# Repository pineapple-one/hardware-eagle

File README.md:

# hardware-eagle
Hardware design files in Autodesk Eagle

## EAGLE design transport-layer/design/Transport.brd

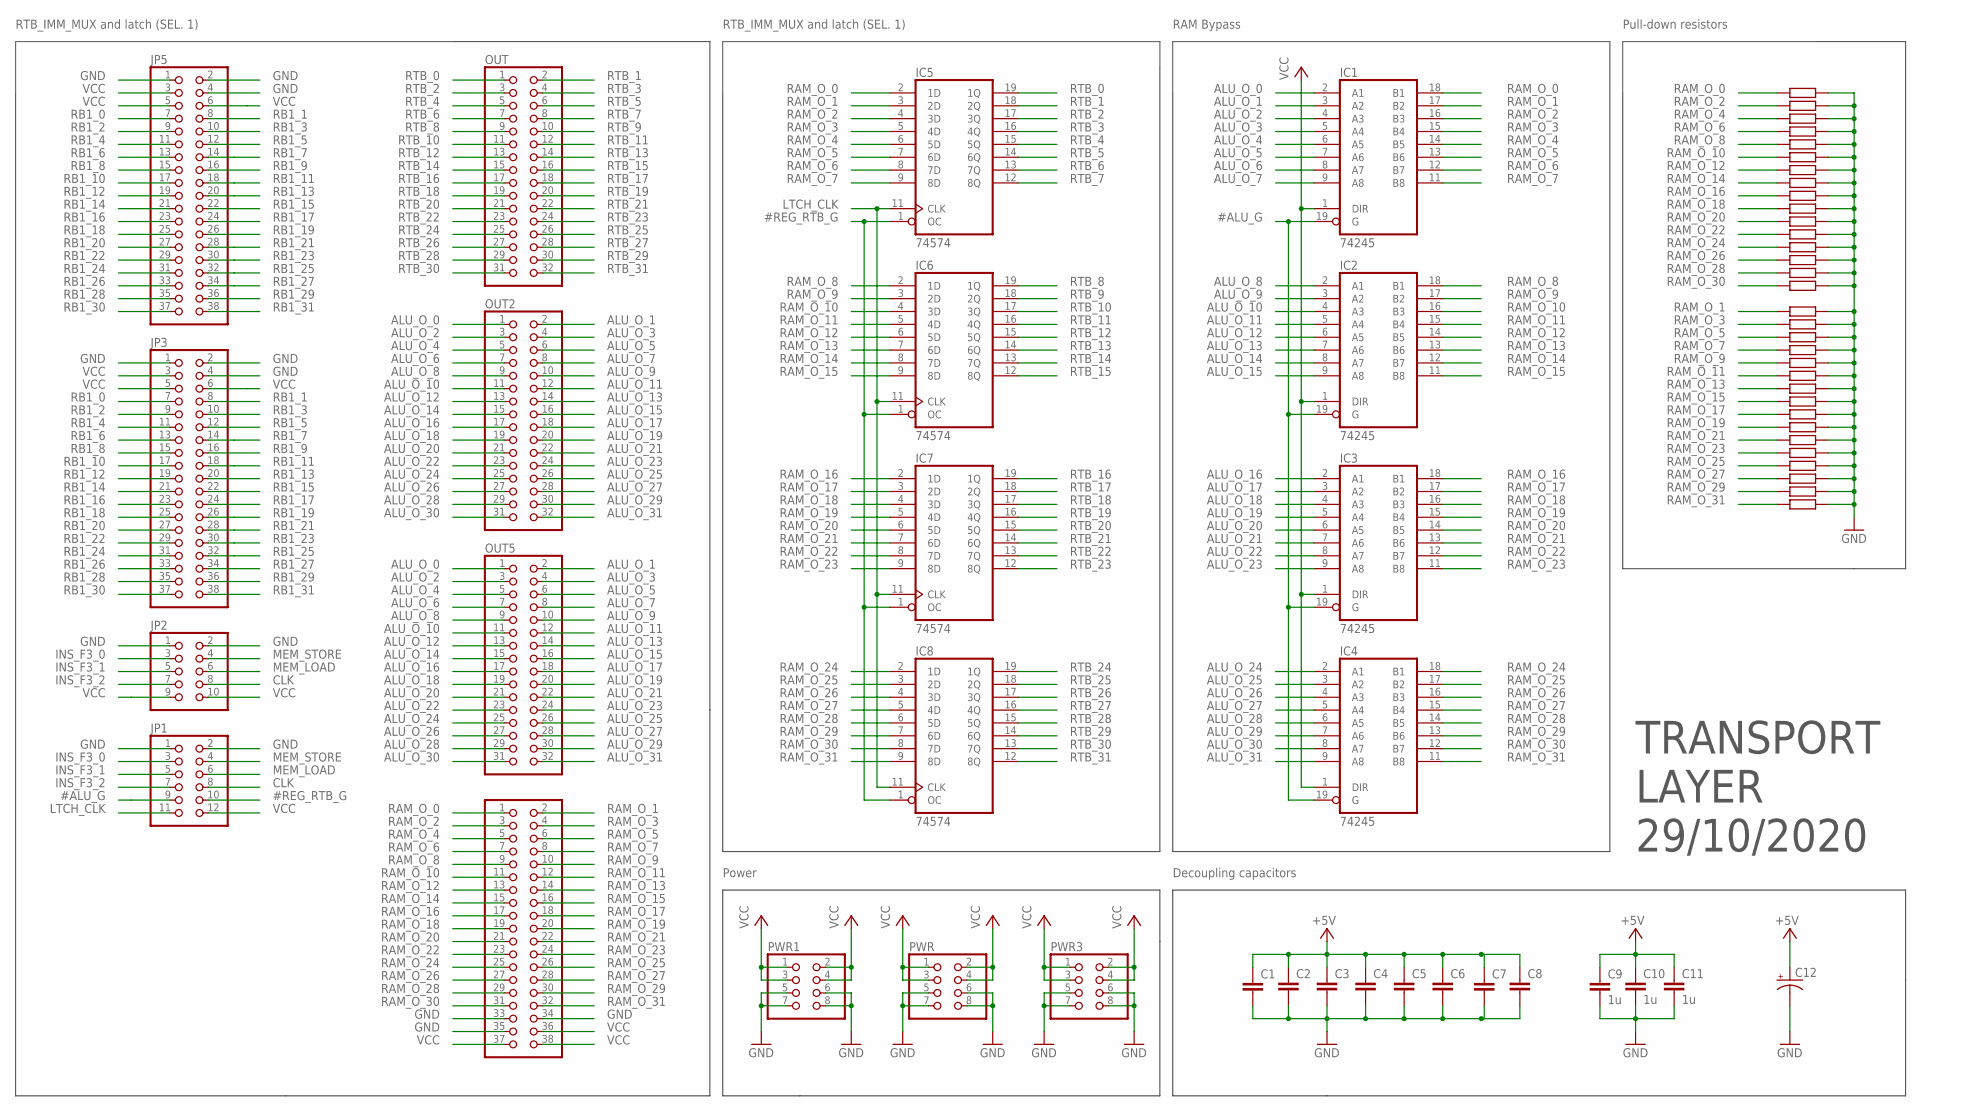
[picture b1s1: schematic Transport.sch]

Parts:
C1, C2, C3, C4, C5, C6, C7, C8: C-EUC0805; C0805
C9, C10, C11: 1u; C0805
C12: CAPACITOR-P153CLV-1010; 153CLV-1010
IC1, IC2, IC3, IC4: 74245; TSSOP20
IC5, IC6, IC7, IC8: 74574; TSSOP20
JP1: PINHD-2X6; 2X06
JP2: PINHD-2X5; 2X05
JP3, JP4, JP5: PINHD-2X19; 2X19
OUT, OUT2, OUT5: PINHD-2X16; 2X16
PWR, PWR1, PWR3: PINHD-2X4; 2X04
R1, R2, R3, R4, R5, R6, R7, R8, R9, R10, R11, R12, R13, R14, R15, R16, R17, R18, R19, R20, R21, R22, R23, R24, R25, R26, R27, R28, R29, R30, R31, R33: R-EU_R0805; R0805

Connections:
#ALU_G: IC1.19 (G), IC2.19 (G), IC3.19 (G), IC4.19 (G), JP1.9
#REG_RTB_G: IC5.1 (OC), IC6.1 (OC), IC7.1 (OC), IC8.1 (OC), JP1.10
ALU_O_0: IC1.2 (A1), OUT2.1, OUT5.1
ALU_O_1: IC1.3 (A2), OUT2.2, OUT5.2
ALU_O_2: IC1.4 (A3), OUT2.3, OUT5.3
ALU_O_3: IC1.5 (A4), OUT2.4, OUT5.4
ALU_O_4: IC1.6 (A5), OUT2.5, OUT5.5
ALU_O_5: IC1.7 (A6), OUT2.6, OUT5.6
ALU_O_6: IC1.8 (A7), OUT2.7, OUT5.7
ALU_O_7: IC1.9 (A8), OUT2.8, OUT5.8
ALU_O_8: IC2.2 (A1), OUT2.9, OUT5.9
ALU_O_9: IC2.3 (A2), OUT2.10, OUT5.10
ALU_O_10: IC2.4 (A3), OUT2.11, OUT5.11
ALU_O_11: IC2.5 (A4), OUT2.12, OUT5.12
ALU_O_12: IC2.6 (A5), OUT2.13, OUT5.13
ALU_O_13: IC2.7 (A6), OUT2.14, OUT5.14
ALU_O_14: IC2.8 (A7), OUT2.15, OUT5.15
ALU_O_15: IC2.9 (A8), OUT2.16, OUT5.16
ALU_O_16: IC3.2 (A1), OUT2.17, OUT5.17
ALU_O_17: IC3.3 (A2), OUT2.18, OUT5.18
ALU_O_18: IC3.4 (A3), OUT2.19, OUT5.19
ALU_O_19: IC3.5 (A4), OUT2.20, OUT5.20
ALU_O_20: IC3.6 (A5), OUT2.21, OUT5.21
ALU_O_21: IC3.7 (A6), OUT2.22, OUT5.22
ALU_O_22: IC3.8 (A7), OUT2.23, OUT5.23
ALU_O_23: IC3.9 (A8), OUT2.24, OUT5.24
ALU_O_24: IC4.2 (A1), OUT2.25, OUT5.25
ALU_O_25: IC4.3 (A2), OUT2.26, OUT5.26
ALU_O_26: IC4.4 (A3), OUT2.27, OUT5.27
ALU_O_27: IC4.5 (A4), OUT2.28, OUT5.28
ALU_O_28: IC4.6 (A5), OUT2.29, OUT5.29
ALU_O_29: IC4.7 (A6), OUT2.30, OUT5.30
ALU_O_30: IC4.8 (A7), OUT2.31, OUT5.31
ALU_O_31: IC4.9 (A8), OUT2.32, OUT5.32
CLK: JP1.8, JP2.8
GND: C1.2, C2.2, C3.2, C4.2, C5.2, C6.2, C7.2, C8.2, C9.2, C10.2, C11.2, C12.-, IC1.10 (GND), IC2.10 (GND), IC3.10 (GND), IC4.10 (GND), IC5.10 (GND), IC6.10 (GND), IC7.10 (GND), IC8.10 (GND), JP1.1, JP1.2, JP2.1, JP2.2, JP3.1, JP3.2, JP3.4, JP4.33, JP4.34, JP4.35, JP5.1, JP5.2, JP5.4, PWR.5, PWR.6, PWR.7, PWR.8, PWR1.5, PWR1.6, PWR1.7, PWR1.8, PWR3.5, PWR3.6, PWR3.7, PWR3.8, R1.2, R2.2, R3.2, R4.2, R5.2, R6.2, R7.2, R8.2, R9.2, R10.2, R11.2, R12.2, R13.2, R14.2, R15.2, R16.2, R17.2, R18.2, R19.2, R20.2, R21.2, R22.2, R23.2, R24.2, R25.2, R26.2, R27.2, R28.2, R29.2, R30.2, R31.2, R33.2
INS_F3_0: JP1.3, JP2.3
INS_F3_1: JP1.5, JP2.5
INS_F3_2: JP1.7, JP2.7
LTCH_CLK: IC5.11 (CLK), IC6.11 (CLK), IC7.11 (CLK), IC8.11 (CLK), JP1.11
MEM_LOAD: JP1.6, JP2.6
MEM_STORE: JP1.4, JP2.4
RAM_O_0: IC1.18 (B1), IC5.2 (1D), JP4.1, R33.1
RAM_O_1: IC1.17 (B2), IC5.3 (2D), JP4.2, R16.1
RAM_O_2: IC1.16 (B3), IC5.4 (3D), JP4.3, R1.1
RAM_O_3: IC1.15 (B4), IC5.5 (4D), JP4.4, R17.1
RAM_O_4: IC1.14 (B5), IC5.6 (5D), JP4.5, R2.1
RAM_O_5: IC1.13 (B6), IC5.7 (6D), JP4.6, R18.1
RAM_O_6: IC1.12 (B7), IC5.8 (7D), JP4.7, R3.1
RAM_O_7: IC1.11 (B8), IC5.9 (8D), JP4.8, R19.1
RAM_O_8: IC2.18 (B1), IC6.2 (1D), JP4.9, R4.1
RAM_O_9: IC2.17 (B2), IC6.3 (2D), JP4.10, R20.1
RAM_O_10: IC2.16 (B3), IC6.4 (3D), JP4.11, R5.1
RAM_O_11: IC2.15 (B4), IC6.5 (4D), JP4.12, R21.1
RAM_O_12: IC2.14 (B5), IC6.6 (5D), JP4.13, R6.1
RAM_O_13: IC2.13 (B6), IC6.7 (6D), JP4.14, R22.1
RAM_O_14: IC2.12 (B7), IC6.8 (7D), JP4.15, R7.1
RAM_O_15: IC2.11 (B8), IC6.9 (8D), JP4.16, R23.1
RAM_O_16: IC3.18 (B1), IC7.2 (1D), JP4.17, R8.1
RAM_O_17: IC3.17 (B2), IC7.3 (2D), JP4.18, R24.1
RAM_O_18: IC3.16 (B3), IC7.4 (3D), JP4.19, R9.1
RAM_O_19: IC3.15 (B4), IC7.5 (4D), JP4.20, R25.1
RAM_O_20: IC3.14 (B5), IC7.6 (5D), JP4.21, R10.1
RAM_O_21: IC3.13 (B6), IC7.7 (6D), JP4.22, R26.1
RAM_O_22: IC3.12 (B7), IC7.8 (7D), JP4.23, R11.1
RAM_O_23: IC3.11 (B8), IC7.9 (8D), JP4.24, R27.1
RAM_O_24: IC4.18 (B1), IC8.2 (1D), JP4.25, R12.1
RAM_O_25: IC4.17 (B2), IC8.3 (2D), JP4.26, R28.1
RAM_O_26: IC4.16 (B3), IC8.4 (3D), JP4.27, R13.1
RAM_O_27: IC4.15 (B4), IC8.5 (4D), JP4.28, R29.1
RAM_O_28: IC4.14 (B5), IC8.6 (5D), JP4.29, R14.1
RAM_O_29: IC4.13 (B6), IC8.7 (6D), JP4.30, R30.1
RAM_O_30: IC4.12 (B7), IC8.8 (7D), JP4.31, R15.1
RAM_O_31: IC4.11 (B8), IC8.9 (8D), JP4.32, R31.1
RB1_0: JP3.7, JP5.7
RB1_1: JP3.8, JP5.8
RB1_2: JP3.9, JP5.9
RB1_3: JP3.10, JP5.10
RB1_4: JP3.11, JP5.11
RB1_5: JP3.12, JP5.12
RB1_6: JP3.13, JP5.13
RB1_7: JP3.14, JP5.14
RB1_8: JP3.15, JP5.15
RB1_9: JP3.16, JP5.16
RB1_10: JP3.17, JP5.17
RB1_11: JP3.18, JP5.18
RB1_12: JP3.19, JP5.19
RB1_13: JP3.20, JP5.20
RB1_14: JP3.21, JP5.21
RB1_15: JP3.22, JP5.22
RB1_16: JP3.23, JP5.23
RB1_17: JP3.24, JP5.24
RB1_18: JP3.25, JP5.25
RB1_19: JP3.26, JP5.26
RB1_20: JP3.27, JP5.27
RB1_21: JP3.28, JP5.28
RB1_22: JP3.29, JP5.29
RB1_23: JP3.30, JP5.30
RB1_24: JP3.31, JP5.31
RB1_25: JP3.32, JP5.32
RB1_26: JP3.33, JP5.33
RB1_27: JP3.34, JP5.34
RB1_28: JP3.35, JP5.35
RB1_29: JP3.36, JP5.36
RB1_30: JP3.37, JP5.37
RB1_31: JP3.38, JP5.38
RTB_0: IC5.19 (1Q), OUT.1
RTB_1: IC5.18 (2Q), OUT.2
RTB_2: IC5.17 (3Q), OUT.3
RTB_3: IC5.16 (4Q), OUT.4
RTB_4: IC5.15 (5Q), OUT.5
RTB_5: IC5.14 (6Q), OUT.6
RTB_6: IC5.13 (7Q), OUT.7
RTB_7: IC5.12 (8Q), OUT.8
RTB_8: IC6.19 (1Q), OUT.9
RTB_9: IC6.18 (2Q), OUT.10
RTB_10: IC6.17 (3Q), OUT.11
RTB_11: IC6.16 (4Q), OUT.12
RTB_12: IC6.15 (5Q), OUT.13
RTB_13: IC6.14 (6Q), OUT.14
RTB_14: IC6.13 (7Q), OUT.15
RTB_15: IC6.12 (8Q), OUT.16
RTB_16: IC7.19 (1Q), OUT.17
RTB_17: IC7.18 (2Q), OUT.18
RTB_18: IC7.17 (3Q), OUT.19
RTB_19: IC7.16 (4Q), OUT.20
RTB_20: IC7.15 (5Q), OUT.21
RTB_21: IC7.14 (6Q), OUT.22
RTB_22: IC7.13 (7Q), OUT.23
RTB_23: IC7.12 (8Q), OUT.24
RTB_24: IC8.19 (1Q), OUT.25
RTB_25: IC8.18 (2Q), OUT.26
RTB_26: IC8.17 (3Q), OUT.27
RTB_27: IC8.16 (4Q), OUT.28
RTB_28: IC8.15 (5Q), OUT.29
RTB_29: IC8.14 (6Q), OUT.30
RTB_30: IC8.13 (7Q), OUT.31
RTB_31: IC8.12 (8Q), OUT.32
VCC: C1.1, C2.1, C3.1, C4.1, C5.1, C6.1, C7.1, C8.1, C9.1, C10.1, C11.1, C12.+, IC1.1 (DIR), IC1.20 (VCC), IC2.1 (DIR), IC2.20 (VCC), IC3.1 (DIR), IC3.20 (VCC), IC4.1 (DIR), IC4.20 (VCC), IC5.20 (VCC), IC6.20 (VCC), IC7.20 (VCC), IC8.20 (VCC), JP1.12, JP2.9, JP2.10, JP3.3, JP3.5, JP3.6, JP4.36, JP4.37, JP4.38, JP5.3, JP5.5, JP5.6, PWR.1, PWR.2, PWR.3, PWR.4, PWR1.1, PWR1.2, PWR1.3, PWR1.4, PWR3.1, PWR3.2, PWR3.3, PWR3.4

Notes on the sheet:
RTB_IMM_MUX and latch (SEL. 1)
RAM Bypass
Pull-down resistors
Power
Decoupling capacitors
TRANSPORT LAYER 29/10/2020

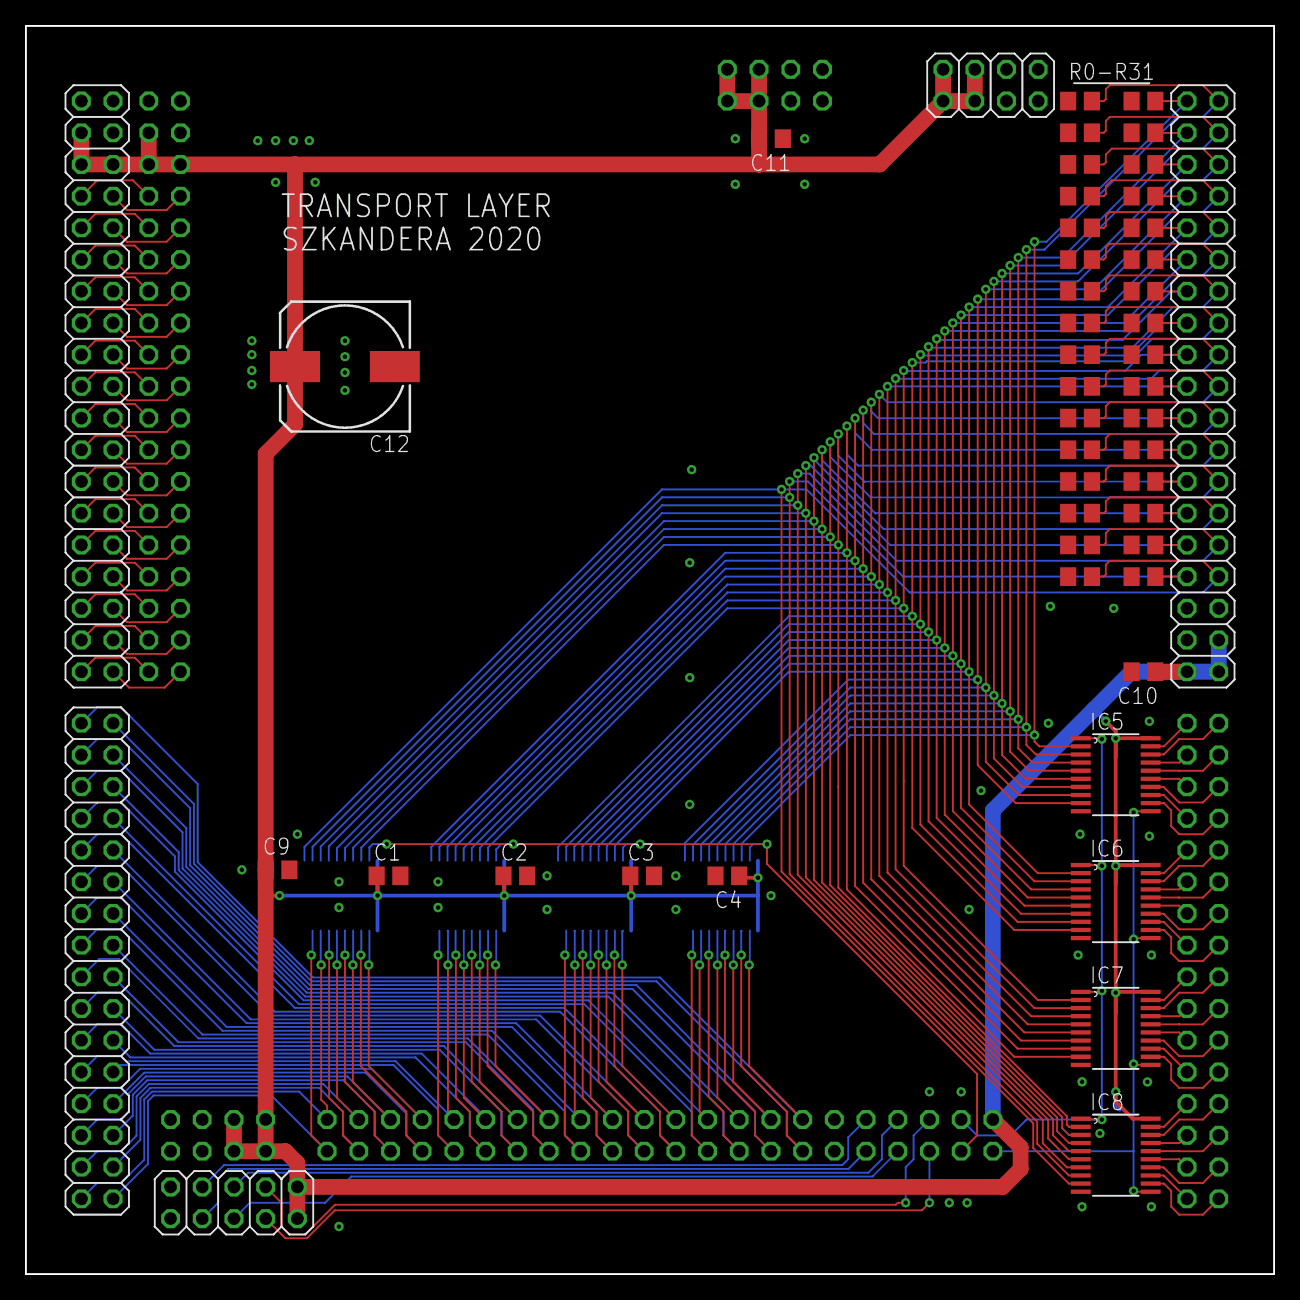
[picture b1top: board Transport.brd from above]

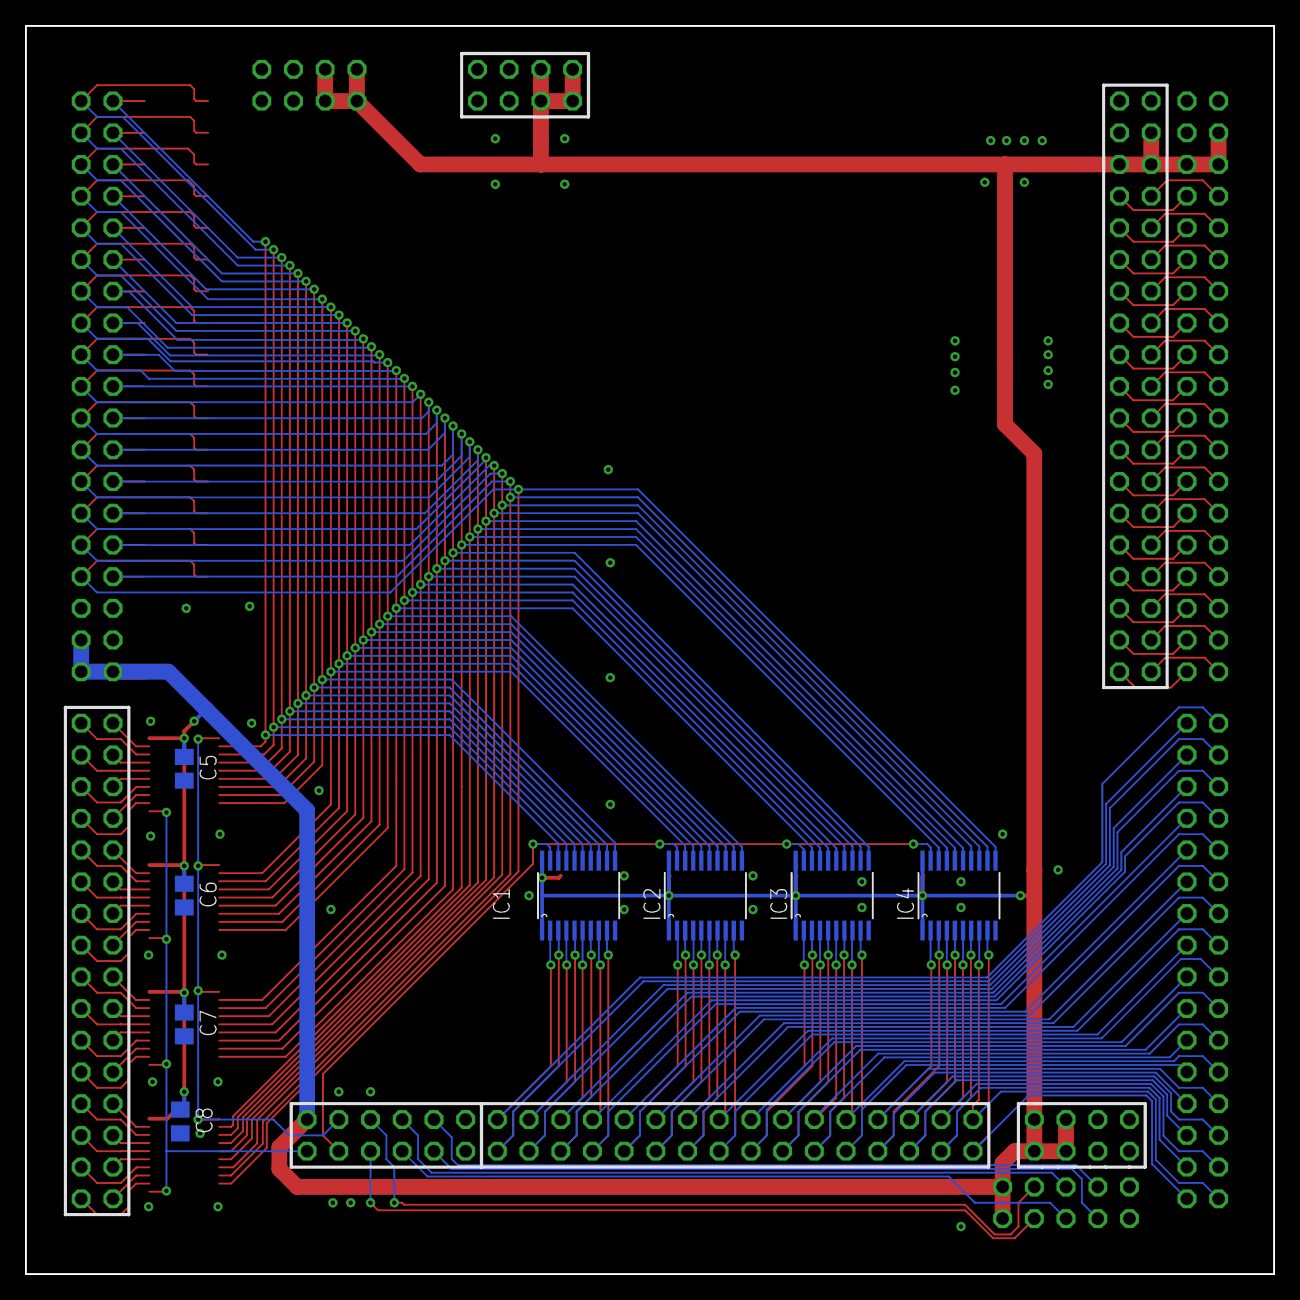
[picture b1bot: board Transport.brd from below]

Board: 2 copper layers, 100.0 x 100.0 mm, 63 parts (8 on the bottom side), 139 nets.

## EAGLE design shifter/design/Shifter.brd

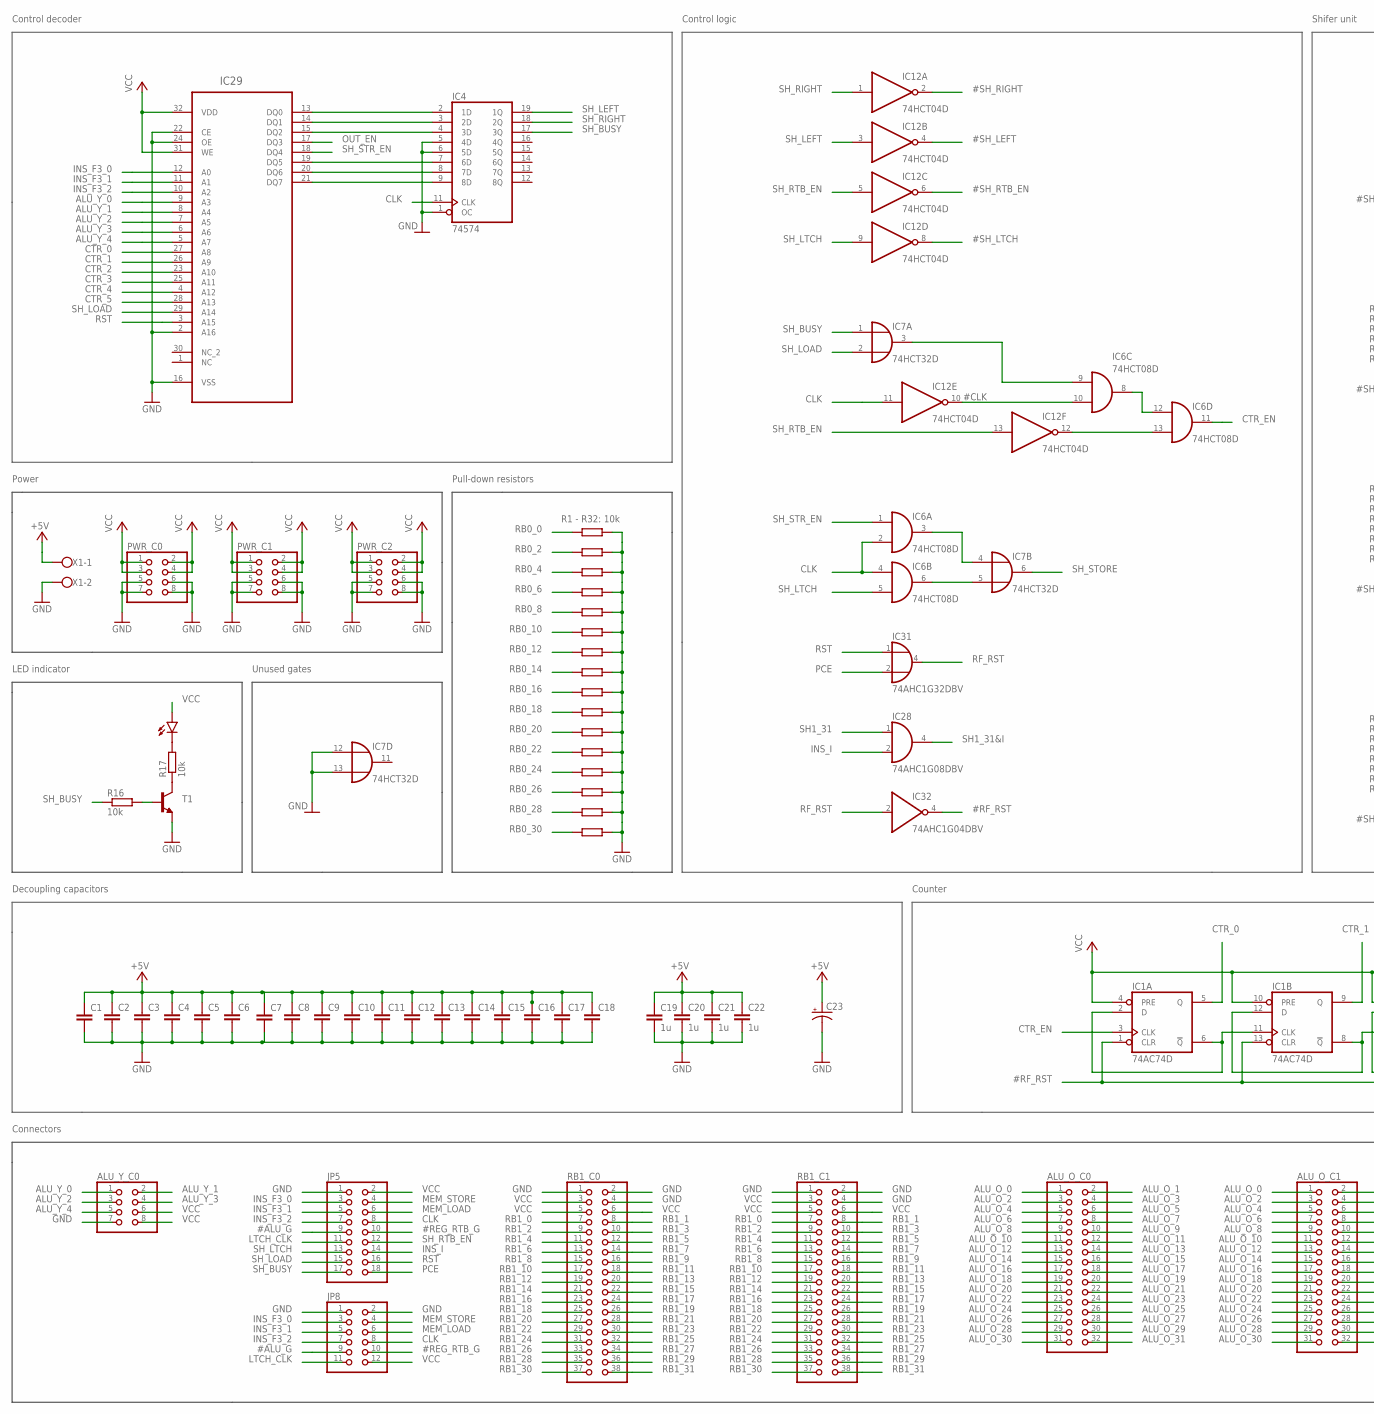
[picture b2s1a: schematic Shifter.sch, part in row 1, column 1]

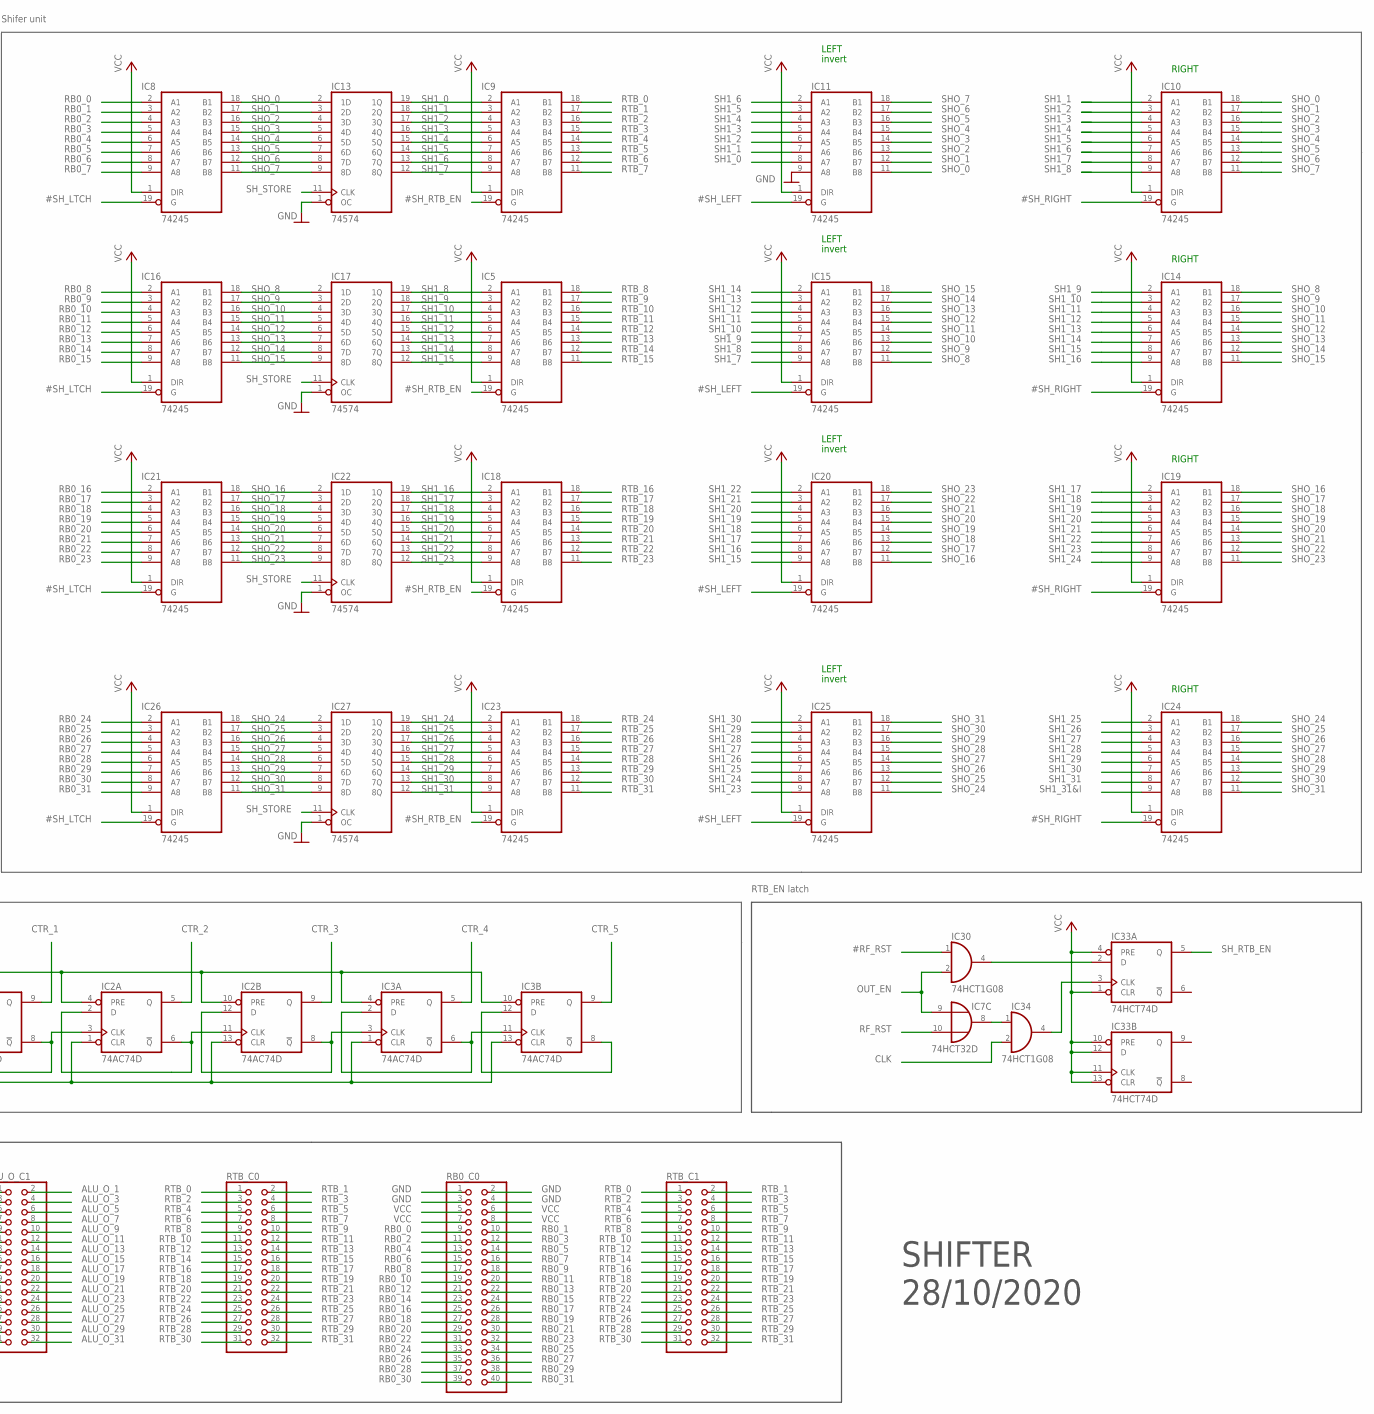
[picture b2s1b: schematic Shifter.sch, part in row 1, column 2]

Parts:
ALU_O_C0, ALU_O_C1: PINHD-2X16; 2X16
ALU_Y_C0: PINHD-2X4; 2X04
C1, C2, C3, C4, C5, C6, C7, C8, C9, C10, C11, C12, C13, C14, C15, C16, C17, C18: C-EUC0805; C0805
C19, C20, C21, C22: 1u; C0805
C23: CAPACITOR-P153CLV-1010; 153CLV-1010
IC1, IC2, IC3: 74AC74D; SO14
IC4, IC13, IC17, IC22, IC27: 74574; TSSOP20
IC5, IC8, IC9, IC10, IC11, IC14, IC15, IC16, IC18, IC19, IC20, IC21, IC23, IC24, IC25, IC26: 74245; TSSOP20
IC6: 74HCT08D; SO14
IC7: 74HCT32D; SO14
IC12: 74HCT04D; SO14
IC28: 74AHC1G08DBV; SOT23-5
IC29: SST39SF010A-70-4I-NHEPLCC32; S32
IC30, IC34: 74HCT1G08; SOT23-5
IC31: 74AHC1G32DBV; SOT23-5
IC32: 74AHC1G04DBV; SOT23-5
IC33: 74HCT74D; SO14
JP5: PINHD-2X9; 2X09
JP8: PINHD-2X6; 2X06
LED1: LEDSML0805; SML0805
PWR_C0, PWR_C1, PWR_C2: PINHD-2X4; 2X04
R0, R1, R2, R3, R4, R5, R6, R7, R8, R9, R10, R11, R12, R13, R14, R15: R-EU_R0805; R0805
R16, R17: 10k; M0805
RB0_C0: PINHD-2X20; 2X20
RB1_C0, RB1_C1: PINHD-2X19; 2X19
RTB_C0, RTB_C1: PINHD-2X16; 2X16
T1: MMBT4401LT1-NPN-SOT23-BEC; SOT23-BEC
X1: W237-102

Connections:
#ALU_G: JP5.9, JP8.9
#CLK: IC6.10 (I1), IC12.10 (O)
#REG_RTB_G: JP5.10, JP8.10
#RF_RST: IC1.1 (CLR), IC1.13 (CLR), IC2.1 (CLR), IC2.13 (CLR), IC3.1 (CLR), IC3.13 (CLR), IC30.1 (I0), IC32.4 (O)
#SH_LEFT: IC11.19 (G), IC12.4 (O), IC15.19 (G), IC20.19 (G), IC25.19 (G)
#SH_LTCH: IC8.19 (G), IC12.8 (O), IC16.19 (G), IC21.19 (G), IC26.19 (G)
#SH_RIGHT: IC10.19 (G), IC12.2 (O), IC14.19 (G), IC19.19 (G), IC24.19 (G)
#SH_RTB_EN: IC5.19 (G), IC9.19 (G), IC12.6 (O), IC18.19 (G), IC23.19 (G)
ALU_O_0: ALU_O_C0.1, ALU_O_C1.1
ALU_O_1: ALU_O_C0.2, ALU_O_C1.2
ALU_O_2: ALU_O_C0.3, ALU_O_C1.3
ALU_O_3: ALU_O_C0.4, ALU_O_C1.4
ALU_O_4: ALU_O_C0.5, ALU_O_C1.5
ALU_O_5: ALU_O_C0.6, ALU_O_C1.6
ALU_O_6: ALU_O_C0.7, ALU_O_C1.7
ALU_O_7: ALU_O_C0.8, ALU_O_C1.8
ALU_O_8: ALU_O_C0.9, ALU_O_C1.9
ALU_O_9: ALU_O_C0.10, ALU_O_C1.10
ALU_O_10: ALU_O_C0.11, ALU_O_C1.11
ALU_O_11: ALU_O_C0.12, ALU_O_C1.12
ALU_O_12: ALU_O_C0.13, ALU_O_C1.13
ALU_O_13: ALU_O_C0.14, ALU_O_C1.14
ALU_O_14: ALU_O_C0.15, ALU_O_C1.15
ALU_O_15: ALU_O_C0.16, ALU_O_C1.16
ALU_O_16: ALU_O_C0.17, ALU_O_C1.17
ALU_O_17: ALU_O_C0.18, ALU_O_C1.18
ALU_O_18: ALU_O_C0.19, ALU_O_C1.19
ALU_O_19: ALU_O_C0.20, ALU_O_C1.20
ALU_O_20: ALU_O_C0.21, ALU_O_C1.21
ALU_O_21: ALU_O_C0.22, ALU_O_C1.22
ALU_O_22: ALU_O_C0.23, ALU_O_C1.23
ALU_O_23: ALU_O_C0.24, ALU_O_C1.24
ALU_O_24: ALU_O_C0.25, ALU_O_C1.25
ALU_O_25: ALU_O_C0.26, ALU_O_C1.26
ALU_O_26: ALU_O_C0.27, ALU_O_C1.27
ALU_O_27: ALU_O_C0.28, ALU_O_C1.28
ALU_O_28: ALU_O_C0.29, ALU_O_C1.29
ALU_O_29: ALU_O_C0.30, ALU_O_C1.30
ALU_O_30: ALU_O_C0.31, ALU_O_C1.31
ALU_O_31: ALU_O_C0.32, ALU_O_C1.32
ALU_Y_0: ALU_Y_C0.1, IC29.9 (A3)
ALU_Y_1: ALU_Y_C0.2, IC29.8 (A4)
ALU_Y_2: ALU_Y_C0.3, IC29.7 (A5)
ALU_Y_3: ALU_Y_C0.4, IC29.6 (A6)
ALU_Y_4: ALU_Y_C0.5, IC29.5 (A7)
CLK: IC4.11 (CLK), IC6.2 (I1), IC6.4 (I0), IC12.11 (I), IC34.2 (I1), JP5.8, JP8.8
CTR_0: IC1.5 (Q), IC29.27 (A8)
CTR_1: IC1.9 (Q), IC29.26 (A9)
CTR_2: IC2.5 (Q), IC29.23 (A10)
CTR_3: IC2.9 (Q), IC29.25 (A11)
CTR_4: IC3.5 (Q), IC29.4 (A12)
CTR_5: IC3.9 (Q), IC29.28 (A13)
CTR_EN: IC1.3 (CLK), IC6.11 (O)
GND: ALU_Y_C0.7, C1.2, C2.2, C3.2, C4.2, C5.2, C6.2, C7.2, C8.2, C9.2, C10.2, C11.2, C12.2, C13.2, C14.2, C15.2, C16.2, C17.2, C18.2, C19.2, C20.2, C21.2, C22.2, C23.-, IC1.7 (GND), IC2.7 (GND), IC3.7 (GND), IC4.1 (OC), IC4.5 (4D), IC4.6 (5D), IC4.10 (GND), IC5.10 (GND), IC6.7 (GND), IC7.7 (GND), IC7.12 (I0), IC7.13 (I1), IC8.10 (GND), IC9.10 (GND), IC10.10 (GND), IC11.9 (A8), IC11.10 (GND), IC12.7 (GND), IC13.1 (OC), IC13.10 (GND), IC14.10 (GND), IC15.10 (GND), IC16.10 (GND), IC17.1 (OC), IC17.10 (GND), IC18.10 (GND), IC19.10 (GND), IC20.10 (GND), IC21.10 (GND), IC22.1 (OC), IC22.10 (GND), IC23.10 (GND), IC24.10 (GND), IC25.10 (GND), IC26.10 (GND), IC27.1 (OC), IC27.10 (GND), IC28.3 (GND), IC29.2 (A16), IC29.16 (VSS), IC29.22 (CE), IC29.24 (OE), IC30.3 (GND), IC31.3 (GND), IC32.3 (GND), IC33.7 (GND), IC34.3 (GND), JP5.1, JP8.1, JP8.2, PWR_C0.5, PWR_C0.6, PWR_C0.7, PWR_C0.8, PWR_C1.5, PWR_C1.6, PWR_C1.7, PWR_C1.8, PWR_C2.5, PWR_C2.6, PWR_C2.7, PWR_C2.8, R0.2, R1.2, R2.2, R3.2, R4.2, R5.2, R6.2, R7.2, R8.2, R9.2, R10.2, R11.2, R12.2, R13.2, R14.2, R15.2, RB0_C0.1, RB0_C0.2, RB0_C0.3, RB0_C0.4, RB1_C0.1, RB1_C0.2, RB1_C0.4, RB1_C1.1, RB1_C1.2, RB1_C1.4, T1.E, X1.2
INS_F3_0: IC29.12 (A0), JP5.3, JP8.3
INS_F3_1: IC29.11 (A1), JP5.5, JP8.5
INS_F3_2: IC29.10 (A2), JP5.7, JP8.7
INS_I: IC28.2 (I1), JP5.14
LTCH_CLK: JP5.11, JP8.11
MEM_LOAD: JP5.6, JP8.6
MEM_STORE: JP5.4, JP8.4
unnamed: IC1.2 (D), IC1.6 (!Q), IC1.11 (CLK)
unnamed: IC4.2 (1D), IC29.13 (DQ0)
unnamed: IC4.3 (2D), IC29.14 (DQ1)
unnamed: IC4.4 (3D), IC29.15 (DQ2)
unnamed: IC3.2 (D), IC3.6 (!Q), IC3.11 (CLK)
unnamed: IC3.8 (!Q), IC3.12 (D)
unnamed: IC1.8 (!Q), IC1.12 (D), IC2.3 (CLK)
unnamed: IC7.8 (O), IC34.1 (I0)
unnamed: IC2.2 (D), IC2.6 (!Q), IC2.11 (CLK)
unnamed: IC30.4 (O), IC33.2 (D)
unnamed: IC4.7 (6D), IC29.19 (DQ5)
unnamed: IC4.8 (7D), IC29.20 (DQ6)
unnamed: IC2.8 (!Q), IC2.12 (D), IC3.3 (CLK)
unnamed: IC4.9 (8D), IC29.21 (DQ7)
unnamed: IC6.9 (I0), IC7.3 (O)
unnamed: IC6.8 (O), IC6.12 (I0)
unnamed: IC6.13 (I1), IC12.12 (O)
unnamed: IC33.3 (CLK), IC34.4 (O)
unnamed: IC6.6 (O), IC7.5 (I1)
unnamed: R16.2, T1.B
unnamed: LED1.C, R17.2
unnamed: R17.1, T1.C
OUT_EN: IC7.9 (I0), IC29.17 (DQ3), IC30.2 (I1)
PCE: IC31.2 (I1), JP5.18
RB0_0: IC8.2 (A1), R0.1, RB0_C0.9
RB0_1: IC8.3 (A2), RB0_C0.10
RB0_2: IC8.4 (A3), R1.1, RB0_C0.11
RB0_3: IC8.5 (A4), RB0_C0.12
RB0_4: IC8.6 (A5), R2.1, RB0_C0.13
RB0_5: IC8.7 (A6), RB0_C0.14
RB0_6: IC8.8 (A7), R3.1, RB0_C0.15
RB0_7: IC8.9 (A8), RB0_C0.16
RB0_8: IC16.2 (A1), R4.1, RB0_C0.17
RB0_9: IC16.3 (A2), RB0_C0.18
RB0_10: IC16.4 (A3), R5.1, RB0_C0.19
RB0_11: IC16.5 (A4), RB0_C0.20
RB0_12: IC16.6 (A5), R6.1, RB0_C0.21
RB0_13: IC16.7 (A6), RB0_C0.22
RB0_14: IC16.8 (A7), R7.1, RB0_C0.23
RB0_15: IC16.9 (A8), RB0_C0.24
RB0_16: IC21.2 (A1), R8.1, RB0_C0.25
RB0_17: IC21.3 (A2), RB0_C0.26
RB0_18: IC21.4 (A3), R9.1, RB0_C0.27
RB0_19: IC21.5 (A4), RB0_C0.28
RB0_20: IC21.6 (A5), R10.1, RB0_C0.29
RB0_21: IC21.7 (A6), RB0_C0.30
RB0_22: IC21.8 (A7), R11.1, RB0_C0.31
RB0_23: IC21.9 (A8), RB0_C0.32
RB0_24: IC26.2 (A1), R12.1, RB0_C0.33
RB0_25: IC26.3 (A2), RB0_C0.34
RB0_26: IC26.4 (A3), R13.1, RB0_C0.35
RB0_27: IC26.5 (A4), RB0_C0.36
RB0_28: IC26.6 (A5), R14.1, RB0_C0.37
RB0_29: IC26.7 (A6), RB0_C0.38
RB0_30: IC26.8 (A7), R15.1, RB0_C0.39
RB0_31: IC26.9 (A8), RB0_C0.40
RB1_0: RB1_C0.7, RB1_C1.7
RB1_1: RB1_C0.8, RB1_C1.8
RB1_2: RB1_C0.9, RB1_C1.9
RB1_3: RB1_C0.10, RB1_C1.10
RB1_4: RB1_C0.11, RB1_C1.11
RB1_5: RB1_C0.12, RB1_C1.12
RB1_6: RB1_C0.13, RB1_C1.13
RB1_7: RB1_C0.14, RB1_C1.14
RB1_8: RB1_C0.15, RB1_C1.15
RB1_9: RB1_C0.16, RB1_C1.16
RB1_10: RB1_C0.17, RB1_C1.17
RB1_11: RB1_C0.18, RB1_C1.18
RB1_12: RB1_C0.19, RB1_C1.19
RB1_13: RB1_C0.20, RB1_C1.20
RB1_14: RB1_C0.21, RB1_C1.21
RB1_15: RB1_C0.22, RB1_C1.22
RB1_16: RB1_C0.23, RB1_C1.23
RB1_17: RB1_C0.24, RB1_C1.24
RB1_18: RB1_C0.25, RB1_C1.25
RB1_19: RB1_C0.26, RB1_C1.26
RB1_20: RB1_C0.27, RB1_C1.27
RB1_21: RB1_C0.28, RB1_C1.28
RB1_22: RB1_C0.29, RB1_C1.29
RB1_23: RB1_C0.30, RB1_C1.30
RB1_24: RB1_C0.31, RB1_C1.31
RB1_25: RB1_C0.32, RB1_C1.32
RB1_26: RB1_C0.33, RB1_C1.33
RB1_27: RB1_C0.34, RB1_C1.34
RB1_28: RB1_C0.35, RB1_C1.35
RB1_29: RB1_C0.36, RB1_C1.36
RB1_30: RB1_C0.37, RB1_C1.37
RB1_31: RB1_C0.38, RB1_C1.38
RF_RST: IC7.10 (I1), IC31.4 (O), IC32.2 (I)
RST: IC29.3 (A15), IC31.1 (I0), JP5.16
RTB_0: IC9.18 (B1), RTB_C0.1, RTB_C1.1
RTB_1: IC9.17 (B2), RTB_C0.2, RTB_C1.2
RTB_2: IC9.16 (B3), RTB_C0.3, RTB_C1.3
RTB_3: IC9.15 (B4), RTB_C0.4, RTB_C1.4
RTB_4: IC9.14 (B5), RTB_C0.5, RTB_C1.5
RTB_5: IC9.13 (B6), RTB_C0.6, RTB_C1.6
RTB_6: IC9.12 (B7), RTB_C0.7, RTB_C1.7
RTB_7: IC9.11 (B8), RTB_C0.8, RTB_C1.8
RTB_8: IC5.18 (B1), RTB_C0.9, RTB_C1.9
RTB_9: IC5.17 (B2), RTB_C0.10, RTB_C1.10
RTB_10: IC5.16 (B3), RTB_C0.11, RTB_C1.11
RTB_11: IC5.15 (B4), RTB_C0.12, RTB_C1.12
RTB_12: IC5.14 (B5), RTB_C0.13, RTB_C1.13
RTB_13: IC5.13 (B6), RTB_C0.14, RTB_C1.14
RTB_14: IC5.12 (B7), RTB_C0.15, RTB_C1.15
RTB_15: IC5.11 (B8), RTB_C0.16, RTB_C1.16
RTB_16: IC18.18 (B1), RTB_C0.17, RTB_C1.17
RTB_17: IC18.17 (B2), RTB_C0.18, RTB_C1.18
RTB_18: IC18.16 (B3), RTB_C0.19, RTB_C1.19
RTB_19: IC18.15 (B4), RTB_C0.20, RTB_C1.20
RTB_20: IC18.14 (B5), RTB_C0.21, RTB_C1.21
RTB_21: IC18.13 (B6), RTB_C0.22, RTB_C1.22
RTB_22: IC18.12 (B7), RTB_C0.23, RTB_C1.23
RTB_23: IC18.11 (B8), RTB_C0.24, RTB_C1.24
RTB_24: IC23.18 (B1), RTB_C0.25, RTB_C1.25
RTB_25: IC23.17 (B2), RTB_C0.26, RTB_C1.26
RTB_26: IC23.16 (B3), RTB_C0.27, RTB_C1.27
RTB_27: IC23.15 (B4), RTB_C0.28, RTB_C1.28
RTB_28: IC23.14 (B5), RTB_C0.29, RTB_C1.29
RTB_29: IC23.13 (B6), RTB_C0.30, RTB_C1.30
RTB_30: IC23.12 (B7), RTB_C0.31, RTB_C1.31
RTB_31: IC23.11 (B8), RTB_C0.32, RTB_C1.32
SH1_0: IC9.2 (A1), IC11.8 (A7), IC13.19 (1Q)
SH1_1: IC9.3 (A2), IC10.2 (A1), IC11.7 (A6), IC13.18 (2Q)
SH1_2: IC9.4 (A3), IC10.3 (A2), IC11.6 (A5), IC13.17 (3Q)
SH1_3: IC9.5 (A4), IC10.4 (A3), IC11.5 (A4), IC13.16 (4Q)
SH1_4: IC9.6 (A5), IC10.5 (A4), IC11.4 (A3), IC13.15 (5Q)
SH1_5: IC9.7 (A6), IC10.6 (A5), IC11.3 (A2), IC13.14 (6Q)
SH1_6: IC9.8 (A7), IC10.7 (A6), IC11.2 (A1), IC13.13 (7Q)
SH1_7: IC9.9 (A8), IC10.8 (A7), IC13.12 (8Q), IC15.9 (A8)
SH1_8: IC5.2 (A1), IC10.9 (A8), IC15.8 (A7), IC17.19 (1Q)
SH1_9: IC5.3 (A2), IC14.2 (A1), IC15.7 (A6), IC17.18 (2Q)
SH1_10: IC5.4 (A3), IC14.3 (A2), IC15.6 (A5), IC17.17 (3Q)
SH1_11: IC5.5 (A4), IC14.4 (A3), IC15.5 (A4), IC17.16 (4Q)
SH1_12: IC5.6 (A5), IC14.5 (A4), IC15.4 (A3), IC17.15 (5Q)
SH1_13: IC5.7 (A6), IC14.6 (A5), IC15.3 (A2), IC17.14 (6Q)
SH1_14: IC5.8 (A7), IC14.7 (A6), IC15.2 (A1), IC17.13 (7Q)
SH1_15: IC5.9 (A8), IC14.8 (A7), IC17.12 (8Q), IC20.9 (A8)
SH1_16: IC14.9 (A8), IC18.2 (A1), IC20.8 (A7), IC22.19 (1Q)
SH1_17: IC18.3 (A2), IC19.2 (A1), IC20.7 (A6), IC22.18 (2Q)
SH1_18: IC18.4 (A3), IC19.3 (A2), IC20.6 (A5), IC22.17 (3Q)
SH1_19: IC18.5 (A4), IC19.4 (A3), IC20.5 (A4), IC22.16 (4Q)
SH1_20: IC18.6 (A5), IC19.5 (A4), IC20.4 (A3), IC22.15 (5Q)
SH1_21: IC18.7 (A6), IC19.6 (A5), IC20.3 (A2), IC22.14 (6Q)
SH1_22: IC18.8 (A7), IC19.7 (A6), IC20.2 (A1), IC22.13 (7Q)
SH1_23: IC18.9 (A8), IC19.8 (A7), IC22.12 (8Q), IC25.9 (A8)
SH1_24: IC19.9 (A8), IC23.2 (A1), IC25.8 (A7), IC27.19 (1Q)
SH1_25: IC23.3 (A2), IC24.2 (A1), IC25.7 (A6), IC27.18 (2Q)
SH1_26: IC23.4 (A3), IC24.3 (A2), IC25.6 (A5), IC27.17 (3Q)
SH1_27: IC23.5 (A4), IC24.4 (A3), IC25.5 (A4), IC27.16 (4Q)
SH1_28: IC23.6 (A5), IC24.5 (A4), IC25.4 (A3), IC27.15 (5Q)
SH1_29: IC23.7 (A6), IC24.6 (A5), IC25.3 (A2), IC27.14 (6Q)
SH1_30: IC23.8 (A7), IC24.7 (A6), IC25.2 (A1), IC27.13 (7Q)
SH1_31: IC23.9 (A8), IC24.8 (A7), IC27.12 (8Q), IC28.1 (I0)
SH1_31&I: IC24.9 (A8), IC28.4 (O)
SHO_0: IC8.18 (B1), IC10.18 (B1), IC11.11 (B8), IC13.2 (1D)
SHO_1: IC8.17 (B2), IC10.17 (B2), IC11.12 (B7), IC13.3 (2D)
SHO_2: IC8.16 (B3), IC10.16 (B3), IC11.13 (B6), IC13.4 (3D)
SHO_3: IC8.15 (B4), IC10.15 (B4), IC11.14 (B5), IC13.5 (4D)
SHO_4: IC8.14 (B5), IC10.14 (B5), IC11.15 (B4), IC13.6 (5D)
SHO_5: IC8.13 (B6), IC10.13 (B6), IC11.16 (B3), IC13.7 (6D)
SHO_6: IC8.12 (B7), IC10.12 (B7), IC11.17 (B2), IC13.8 (7D)
SHO_7: IC8.11 (B8), IC10.11 (B8), IC11.18 (B1), IC13.9 (8D)
SHO_8: IC14.18 (B1), IC15.11 (B8), IC16.18 (B1), IC17.2 (1D)
SHO_9: IC14.17 (B2), IC15.12 (B7), IC16.17 (B2), IC17.3 (2D)
SHO_10: IC14.16 (B3), IC15.13 (B6), IC16.16 (B3), IC17.4 (3D)
SHO_11: IC14.15 (B4), IC15.14 (B5), IC16.15 (B4), IC17.5 (4D)
SHO_12: IC14.14 (B5), IC15.15 (B4), IC16.14 (B5), IC17.6 (5D)
SHO_13: IC14.13 (B6), IC15.16 (B3), IC16.13 (B6), IC17.7 (6D)
SHO_14: IC14.12 (B7), IC15.17 (B2), IC16.12 (B7), IC17.8 (7D)
SHO_15: IC14.11 (B8), IC15.18 (B1), IC16.11 (B8), IC17.9 (8D)
SHO_16: IC19.18 (B1), IC20.11 (B8), IC21.18 (B1), IC22.2 (1D)
SHO_17: IC19.17 (B2), IC20.12 (B7), IC21.17 (B2), IC22.3 (2D)
SHO_18: IC19.16 (B3), IC20.13 (B6), IC21.16 (B3), IC22.4 (3D)
SHO_19: IC19.15 (B4), IC20.14 (B5), IC21.15 (B4), IC22.5 (4D)
SHO_20: IC19.14 (B5), IC20.15 (B4), IC21.14 (B5), IC22.6 (5D)
SHO_21: IC19.13 (B6), IC20.16 (B3), IC21.13 (B6), IC22.7 (6D)
SHO_22: IC19.12 (B7), IC20.17 (B2), IC21.12 (B7), IC22.8 (7D)
SHO_23: IC19.11 (B8), IC20.18 (B1), IC21.11 (B8), IC22.9 (8D)
SHO_24: IC24.18 (B1), IC25.11 (B8), IC26.18 (B1), IC27.2 (1D)
SHO_25: IC24.17 (B2), IC25.12 (B7), IC26.17 (B2), IC27.3 (2D)
SHO_26: IC24.16 (B3), IC25.13 (B6), IC26.16 (B3), IC27.4 (3D)
SHO_27: IC24.15 (B4), IC25.14 (B5), IC26.15 (B4), IC27.5 (4D)
SHO_28: IC24.14 (B5), IC25.15 (B4), IC26.14 (B5), IC27.6 (5D)
SHO_29: IC24.13 (B6), IC25.16 (B3), IC26.13 (B6), IC27.7 (6D)
SHO_30: IC24.12 (B7), IC25.17 (B2), IC26.12 (B7), IC27.8 (7D)
SHO_31: IC24.11 (B8), IC25.18 (B1), IC26.11 (B8), IC27.9 (8D)
SH_BUSY: IC4.17 (3Q), IC7.1 (I0), JP5.17, R16.1
SH_EN: IC6.3 (O), IC7.4 (I0)
SH_LEFT: IC4.19 (1Q), IC12.3 (I)
SH_LOAD: IC7.2 (I1), IC29.29 (A14), JP5.15
SH_LTCH: IC6.5 (I1), IC12.9 (I), JP5.13
SH_RIGHT: IC4.18 (2Q), IC12.1 (I)
SH_RTB_EN: IC12.5 (I), IC12.13 (I), IC33.5 (Q), JP5.12
SH_STORE: IC7.6 (O), IC13.11 (CLK), IC17.11 (CLK), IC22.11 (CLK), IC27.11 (CLK)
SH_STR_EN: IC6.1 (I0), IC29.18 (DQ4)
VCC: ALU_Y_C0.6, ALU_Y_C0.8, C1.1, C2.1, C3.1, C4.1, C5.1, C6.1, C7.1, C8.1, C9.1, C10.1, C11.1, C12.1, C13.1, C14.1, C15.1, C16.1, C17.1, C18.1, C19.1, C20.1, C21.1, C22.1, C23.+, IC1.4 (PRE), IC1.10 (PRE), IC1.14 (VCC), IC2.4 (PRE), IC2.10 (PRE), IC2.14 (VCC), IC3.4 (PRE), IC3.10 (PRE), IC3.14 (VCC), IC4.20 (VCC), IC5.1 (DIR), IC5.20 (VCC), IC6.14 (VCC), IC7.14 (VCC), IC8.1 (DIR), IC8.20 (VCC), IC9.1 (DIR), IC9.20 (VCC), IC10.1 (DIR), IC10.20 (VCC), IC11.1 (DIR), IC11.20 (VCC), IC12.14 (VCC), IC13.20 (VCC), IC14.1 (DIR), IC14.20 (VCC), IC15.1 (DIR), IC15.20 (VCC), IC16.1 (DIR), IC16.20 (VCC), IC17.20 (VCC), IC18.1 (DIR), IC18.20 (VCC), IC19.1 (DIR), IC19.20 (VCC), IC20.1 (DIR), IC20.20 (VCC), IC21.1 (DIR), IC21.20 (VCC), IC22.20 (VCC), IC23.1 (DIR), IC23.20 (VCC), IC24.1 (DIR), IC24.20 (VCC), IC25.1 (DIR), IC25.20 (VCC), IC26.1 (DIR), IC26.20 (VCC), IC27.20 (VCC), IC28.5 (VCC), IC29.31 (WE), IC29.32 (VDD), IC30.5 (VCC), IC31.5 (VCC), IC32.5 (VCC), IC33.1 (CLR), IC33.4 (PRE), IC33.10 (PRE), IC33.11 (CLK), IC33.12 (D), IC33.13 (CLR), IC33.14 (VCC), IC34.5 (VCC), JP5.2, JP8.12, LED1.A, PWR_C0.1, PWR_C0.2, PWR_C0.3, PWR_C0.4, PWR_C1.1, PWR_C1.2, PWR_C1.3, PWR_C1.4, PWR_C2.1, PWR_C2.2, PWR_C2.3, PWR_C2.4, RB0_C0.5, RB0_C0.6, RB0_C0.7, RB0_C0.8, RB1_C0.3, RB1_C0.5, RB1_C0.6, RB1_C1.3, RB1_C1.5, RB1_C1.6, X1.1

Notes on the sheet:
LEFT
RIGHT
invert
R1 - R32: 10k
Counter
Shifer unit
Control logic
Control decoder
Decoupling capacitors
Pull-down resistors
Power
Connectors
RTB_EN latch
LED indicator
Unused gates
SHIFTER 28/10/2020

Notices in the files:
parts and their libraries:
SparkFun-Switches: Licensing: Creative Commons ShareAlike 4.0 International - https://creativecommons.org/licenses/by-sa/4.0
74LV: Copyright (C) 2008, Bob Starr
